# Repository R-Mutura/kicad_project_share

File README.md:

# AUTOMATION AGRIBOARD
This board features various sensors and mosules that enables easy monitoring of any environmental variable as well as control of outputs such as fans and heaters.
The board feature an ESP32 SoC that enables use of webservers and BLE configuration. This can be used to control and monitor conditions from your phone or computer.
Applications areas: Green houses and small Gardens.

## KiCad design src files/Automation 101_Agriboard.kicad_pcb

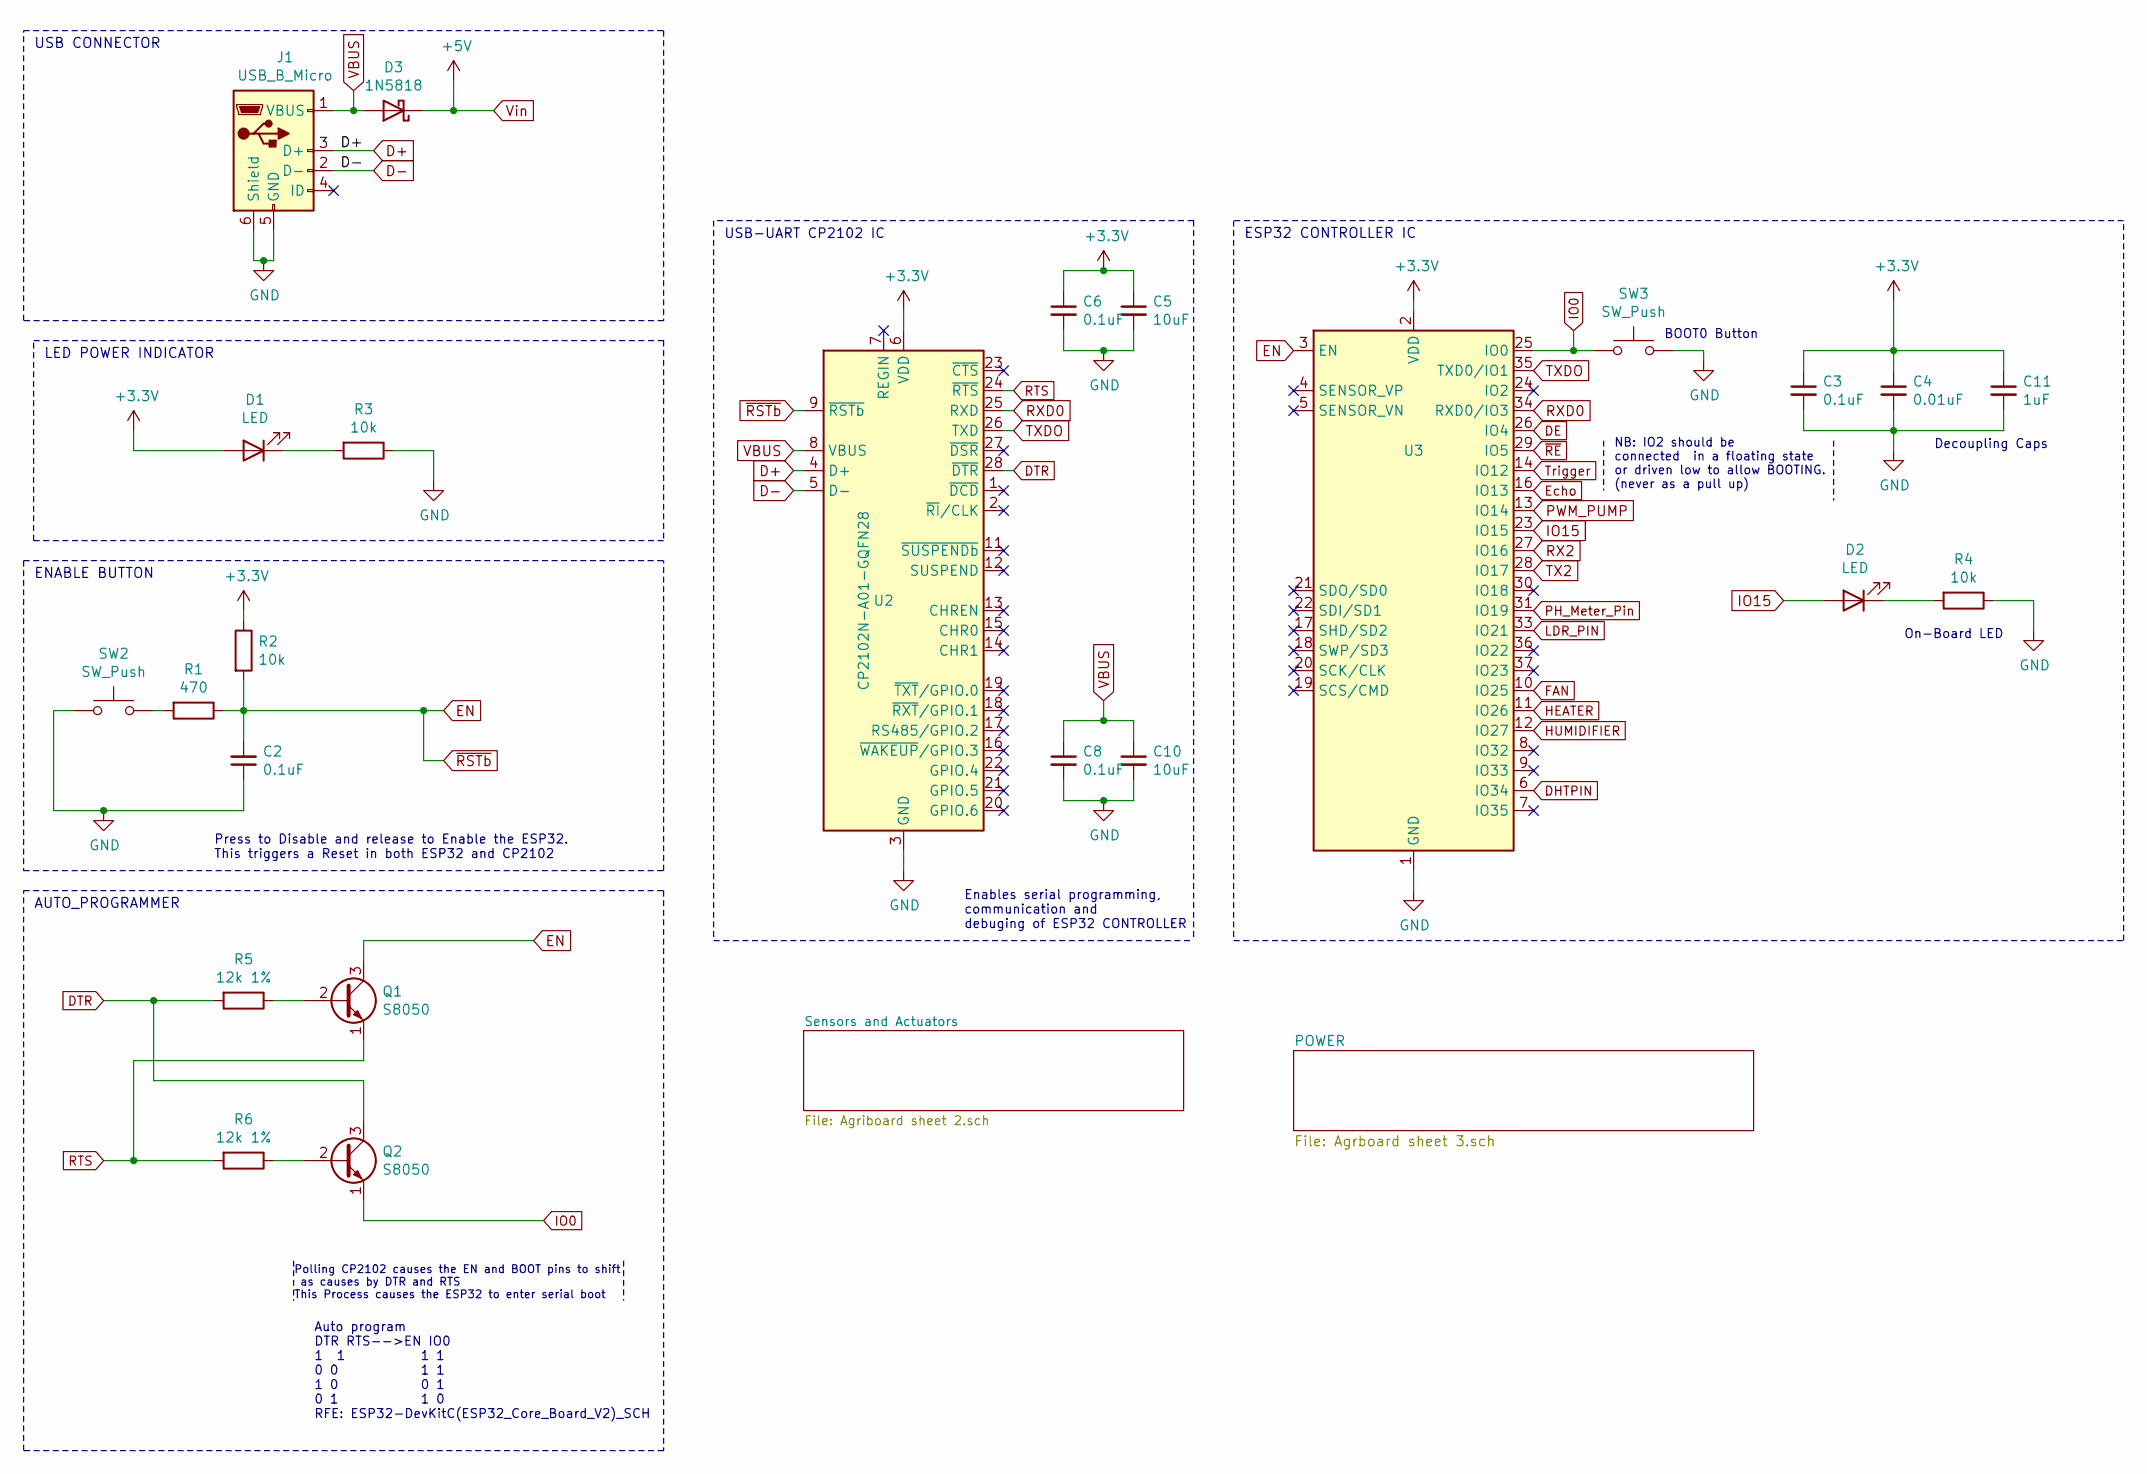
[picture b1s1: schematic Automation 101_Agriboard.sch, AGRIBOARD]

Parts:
C2, C3, C6, C8: 0.1uF; C_0402_1005Metric
C4: 0.01uF; C_0402_1005Metric
C5, C10: 10uF; C_0402_1005Metric
C11: 1uF; C_0402_1005Metric
D1, D2: LED; LED_0402_1005Metric
D3: 1N5818; D_0201_0603Metric_Pad0.64x0.40mm_HandSolder
J1: USB_B_Micro; USB_Micro-B_Molex_47346-0001
Q1, Q2: S8050; TSOT-23
R1: 470; R_0402_1005Metric_Pad0.72x0.64mm_HandSolder
R2, R3, R4: 10k; R_0402_1005Metric
R5, R6: 12k 1%; R_0402_1005Metric_Pad0.72x0.64mm_HandSolder
SW2, SW3: SW_Push; SW_SPST_B3U-1000P-B
U2: CP2102N-A01-GQFN28; QFN-28-1EP_5x5mm_P0.5mm_EP3.35x3.35mm
U3: ESP32-WROOM-32

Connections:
+3V3: C3.1, C4.1, C5.1, C6.1, C11.1, D1.2 (A), R2.1, U2.6 (VDD), U3.2 (VDD); also elsewhere on the board
D+: J1.3 (D+), U2.4 (D+)
D-: J1.2 (D-), U2.5 (D-)
DE: U3.26 (IO4); also elsewhere on the board
DHTPIN: U3.6 (IO34); also elsewhere on the board
DTR: Q2.3 (C), R5.2, U2.28 (~DTR)
EN: C2.2, Q1.3 (C), R1.1, R2.2, U2.9 (~RSTb), U3.3 (EN)
Echo: U3.16 (IO13); also elsewhere on the board
FAN: U3.10 (IO25); also elsewhere on the board
GND: C2.1, C3.2, C4.2, C5.2, C6.2, C8.2, C10.2, C11.2, J1.5 (GND), J1.6 (Shield), R3.1, R4.1, SW2.1, SW3.2, U2.3 (GND), U2.29 (GND), U3.1 (GND), U3.15 (GND), U3.38 (GND), U3.39 (GND); also elsewhere on the board
HEATER: U3.11 (IO26); also elsewhere on the board
HUMIDIFIER: U3.12 (IO27); also elsewhere on the board
IO0: Q2.1 (E), SW3.1, U3.25 (IO0)
IO15: D2.2 (A), U3.23 (IO15)
LDR_PIN: U3.33 (IO21); also elsewhere on the board
unnamed: D1.1 (K), R3.2
unnamed: D2.1 (K), R4.2
unnamed: Q1.2 (B), R5.1
unnamed: Q2.2 (B), R6.1
unnamed: R1.2, SW2.2
PH_Meter_Pin: U3.31 (IO19); also elsewhere on the board
PWM_PUMP: U3.13 (IO14); also elsewhere on the board
RTS: Q1.1 (E), R6.2, U2.24 (~RTS)
RX2: U3.27 (IO16); also elsewhere on the board
RXD0: U2.25 (RXD), U3.34 (RXD0/IO3)
TX2: U3.28 (IO17); also elsewhere on the board
TXDO: U2.26 (TXD), U3.35 (TXD0/IO1)
Trigger: U3.14 (IO12); also elsewhere on the board
VBUS: C8.1, C10.1, D3.2 (A), J1.1 (VBUS), U2.8 (VBUS)
Vin: D3.1 (K); also elsewhere on the board
~RE: U3.29 (IO5); also elsewhere on the board

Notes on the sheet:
USB CONNECTOR
LED POWER INDICATOR
ENABLE BUTTON
Press to Disable and release to Enable the ESP32. This triggers a Reset in both ESP32 and CP2102
USB-UART CP2102 IC
ESP32 CONTROLLER IC
On-Board LED
Decoupling Caps
BOOT0 Button
Auto program DTR RTS-->EN IO0 1 1 1 1 0 0 1 1 1 0 0 1 0 1 1 0 RFE: ESP32-DevKitC(ESP32_Core_Board_V2)_SCH
Enables serial programming, communication and debuging of ESP32 CONTROLLER
AUTO_PROGRAMMER
Polling CP2102 causes the EN and BOOT pins to shift as causes by DTR and RTS This Process causes the ESP32 to enter serial boot
NB: IO2 should be connected in a floating state or driven low to allow BOOTING. (never as a pull up)

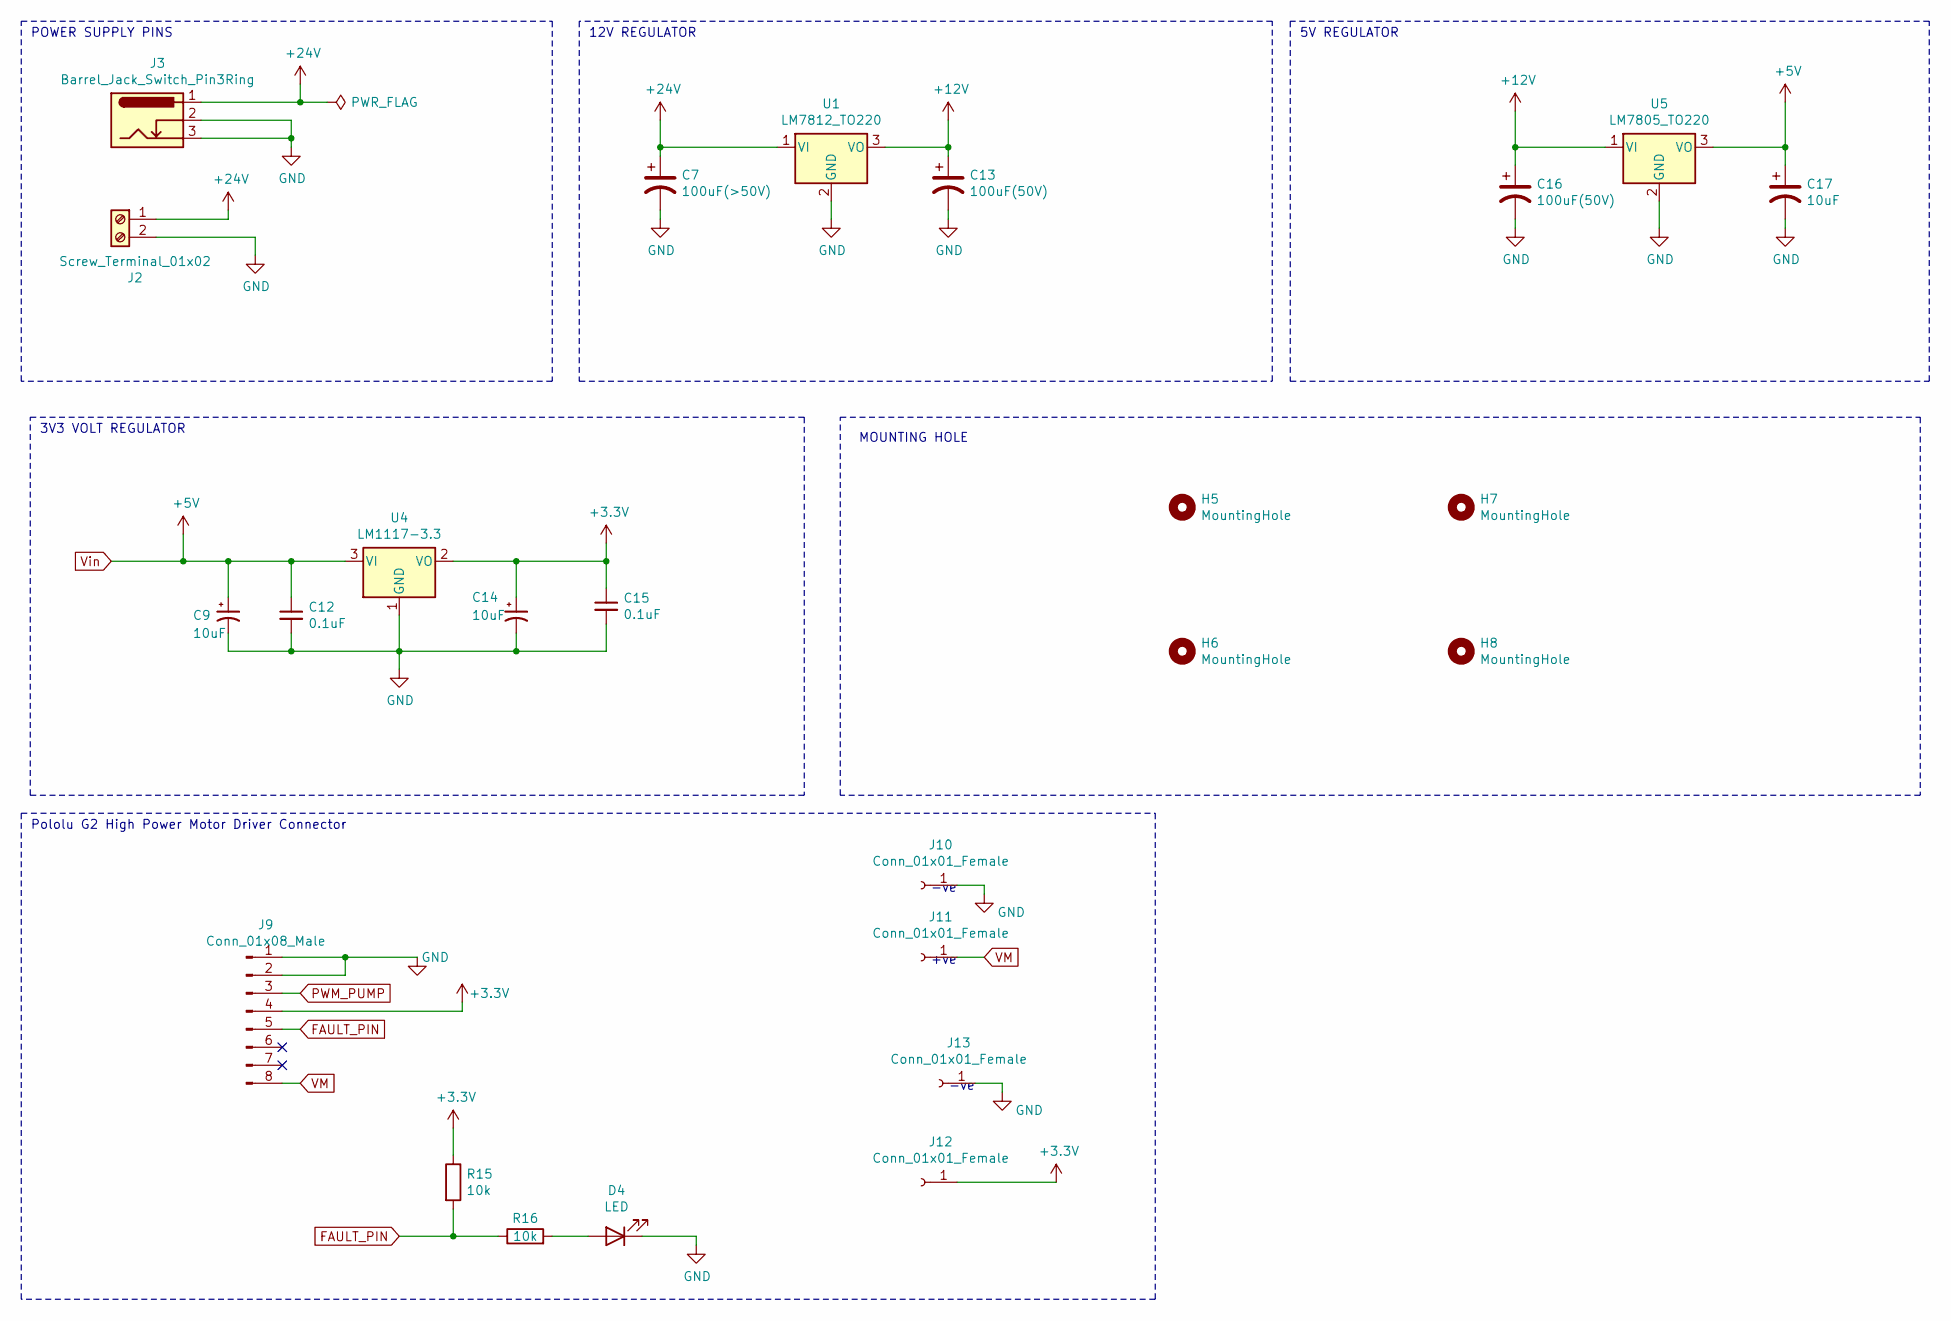
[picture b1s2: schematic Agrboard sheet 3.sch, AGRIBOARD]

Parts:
C7: 100uF(>50V); CP_Radial_D5.0mm_P2.50mm
C9, C14: 10uF; CP_EIA-1608-08_AVX-J_Pad1.25x1.05mm_HandSolder
C12, C15: 0.1uF; C_0402_1005Metric
C13, C16: 100uF(50V); CP_Radial_D5.0mm_P2.50mm
C17: 10uF; CP_Radial_D5.0mm_P2.50mm
D4: LED; LED_0805_2012Metric_Pad1.15x1.40mm_HandSolder
H5, H6, H7, H8: MountingHole; MountingHole_2.5mm
J2: Screw_Terminal_01x02; TerminalBlock_RND_205-00012_1x02_P5.00mm_Horizontal
J3: Barrel_Jack_Switch_Pin3Ring; BarrelJack_Horizontal
J9: Conn_01x08_Male; PinHeader_1x08_P2.54mm_Vertical
J10, J11, J12, J13: Conn_01x01_Female; PinHeader_1x01_P2.54mm_Vertical
R15, R16: 10k; R_0805_2012Metric_Pad1.20x1.40mm_HandSolder
U1: LM7812_TO220; TO-220-3_Vertical
U4: LM1117-3.3; SOT-223-3_TabPin2
U5: LM7805_TO220; TO-220-3_Vertical

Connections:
+3V3: C14.1, C15.1, J9.4, J12.1, R15.1, U4.2 (VO); also elsewhere on the board
+12V: C13.1, C16.1, U1.3 (VO), U5.1 (VI); also elsewhere on the board
+24V: C7.1, J2.1, J3.1, U1.1 (VI)
FAULT_PIN: J9.5, R15.2, R16.1
GND: C7.2, C9.2, C12.2, C13.2, C14.2, C15.2, C16.2, C17.2, D4.1 (K), J2.2, J3.2, J3.3, J9.1, J9.2, J10.1, J13.1, U1.2 (GND), U4.1 (GND), U5.2 (GND); also elsewhere on the board
unnamed: D4.2 (A), R16.2
PWM_PUMP: J9.3; also elsewhere on the board
VM: J9.8, J11.1
Vin: C9.1, C12.1, C17.1, U4.3 (VI), U5.3 (VO); also elsewhere on the board

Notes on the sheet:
3V3 VOLT REGULATOR
POWER SUPPLY PINS
12V REGULATOR
5V REGULATOR
-ve
+ve
Pololu G2 High Power Motor Driver Connector
MOUNTING HOLE

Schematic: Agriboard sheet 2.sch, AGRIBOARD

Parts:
C18: 0.1uF; C_0805_2012Metric_Pad1.18x1.45mm_HandSolder
H1, H2: MountingHole; MountingHole_2.5mm
J4, J6: Conn_01x04_Male; PinHeader_1x04_P2.54mm_Vertical
J5: NPK_SIGNAL_CONNECTOR; TerminalBlock_RND_205-00012_1x02_P5.00mm_Horizontal
J7: Conn_01x03_Female; PinSocket_1x03_P2.54mm_Horizontal
J8: RELAY CONN; PinSocket_1x06_P2.54mm_Vertical
J14: NPK_POWER_CONNECTOR; TerminalBlock_RND_205-00012_1x02_P5.00mm_Horizontal
Q3, Q4, Q5: 2N2222; TO-18-3
R7, R8, R9, R10, R11, R14: 10k; R_0402_1005Metric
R12: R; R_0805_2012Metric_Pad1.20x1.40mm_HandSolder
R13: R_PHOTO; R_LDR_11x9.4mm_P8.2mm_Vertical
U6: MAX3486; SOIC-8_3.9x4.9mm_P1.27mm

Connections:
+3V3: C18.1, J4.1, J6.1, J7.2, J8.6, R12.1, U6.8 (VCC); also elsewhere on the board
+12V: J14.1; also elsewhere on the board
DE: U6.3 (DE); also elsewhere on the board
DHTPIN: J6.2; also elsewhere on the board
Echo: J4.3; also elsewhere on the board
FAN: R9.2; also elsewhere on the board
FAN_RELAY: J8.3, Q4.1
GND: C18.2, J4.4, J6.4, J7.1, J8.1, J14.2, R13.2, U6.5 (GND); also elsewhere on the board
HEATER: R11.2; also elsewhere on the board
HEATER_RELAY: J8.2, Q5.1
HUMIDIFIER: R7.2; also elsewhere on the board
HUMIDIFIER_RELAY: J8.4, Q3.1
LDR_PIN: R12.2, R13.1; also elsewhere on the board
unnamed: J5.1, U6.7 (B)
unnamed: J5.2, U6.6 (A)
unnamed: Q3.2, R7.1
unnamed: Q3.3, R8.2
unnamed: Q4.2, R9.1
unnamed: Q4.3, R10.2
unnamed: Q5.2, R11.1
unnamed: Q5.3, R14.2
PH_Meter_Pin: J7.3; also elsewhere on the board
RX2: U6.1 (RO); also elsewhere on the board
TX2: U6.4 (DI); also elsewhere on the board
Trigger: J4.2; also elsewhere on the board
Vin: R8.1, R10.1, R14.1; also elsewhere on the board
~RE: U6.2 (~RE); also elsewhere on the board

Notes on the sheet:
RS485 TTL CONVERTER
PH SENSOR MODULE
this module features tremperature compensation, and analog signal procesing
TEMPERATURE/HUMIDITY SENSOR
DHT22 SENSOR
LIGHT DETECTOR
LDR SENSOR
NPK sensor connectors
WATER LVEL SENSOR(Ultra_Sonic)
On-Board LED
HEATER ACTUATOR
HUMIDIFIER ACTUATOR
FAN ACTUATOR
RELAY CONNECTOR

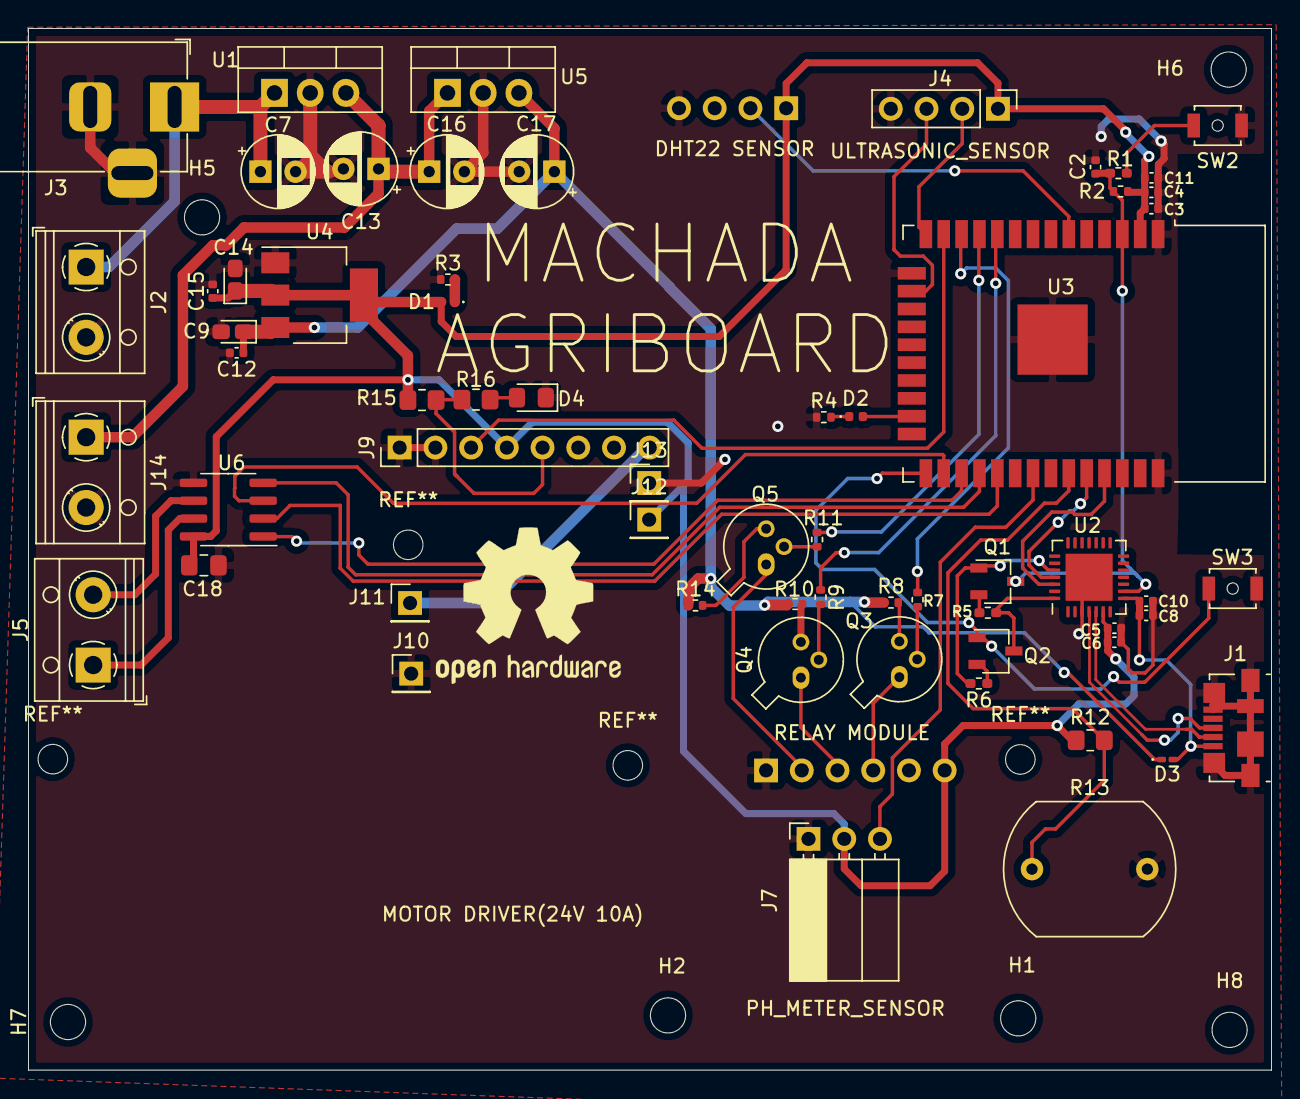
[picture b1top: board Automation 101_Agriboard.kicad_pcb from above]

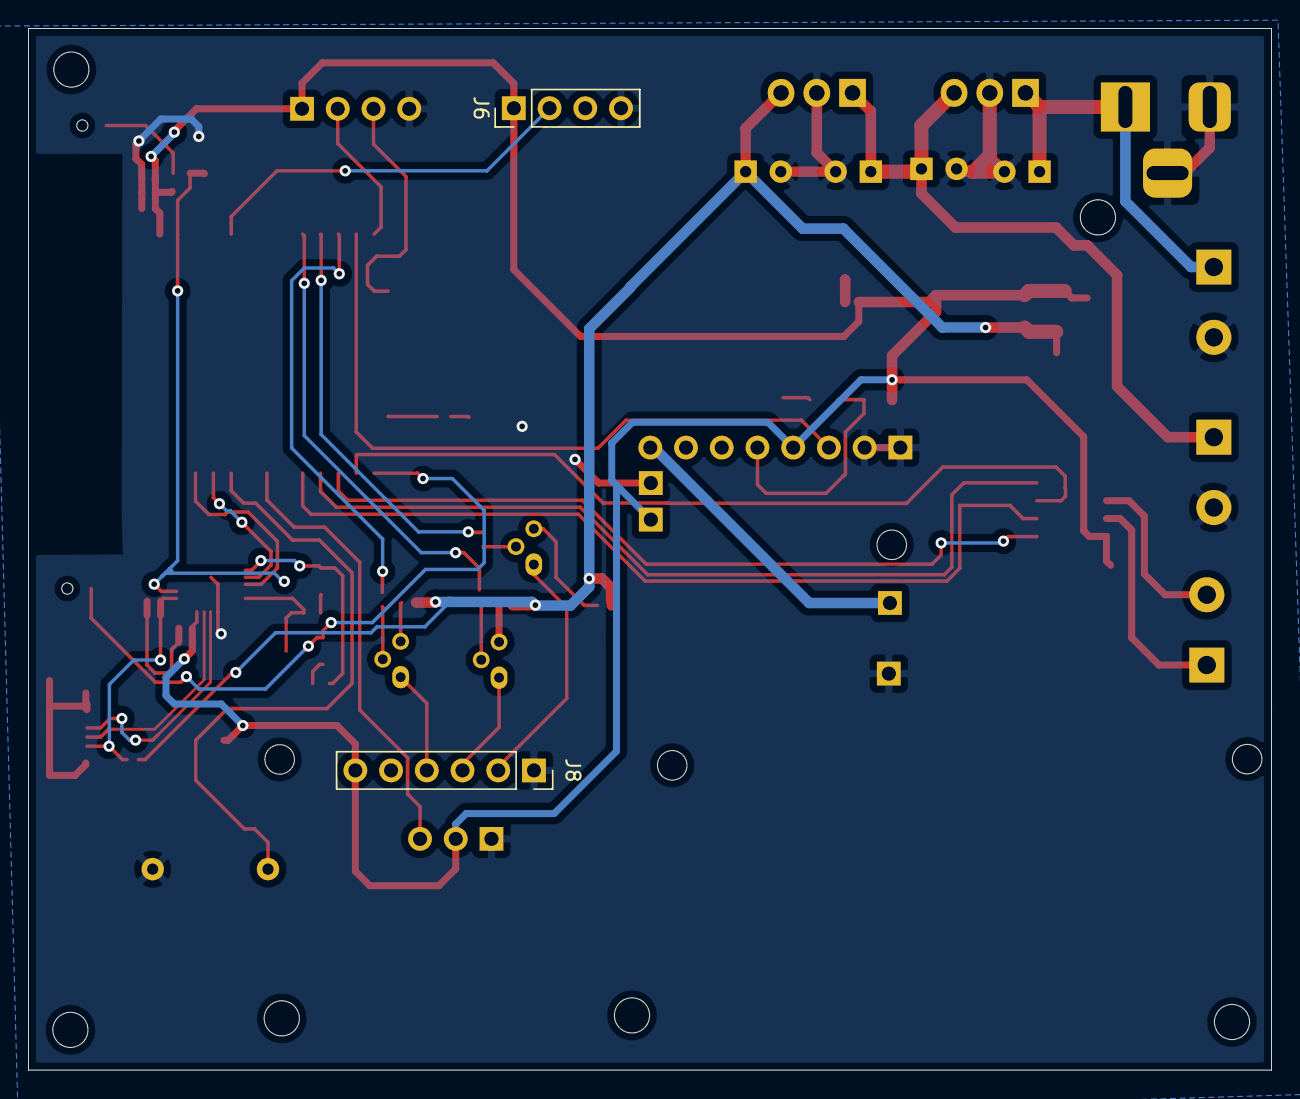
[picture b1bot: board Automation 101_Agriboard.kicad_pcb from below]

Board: 2 copper layers, 88.4 x 74.1 mm, 70 parts (2 on the bottom side), 47 nets.

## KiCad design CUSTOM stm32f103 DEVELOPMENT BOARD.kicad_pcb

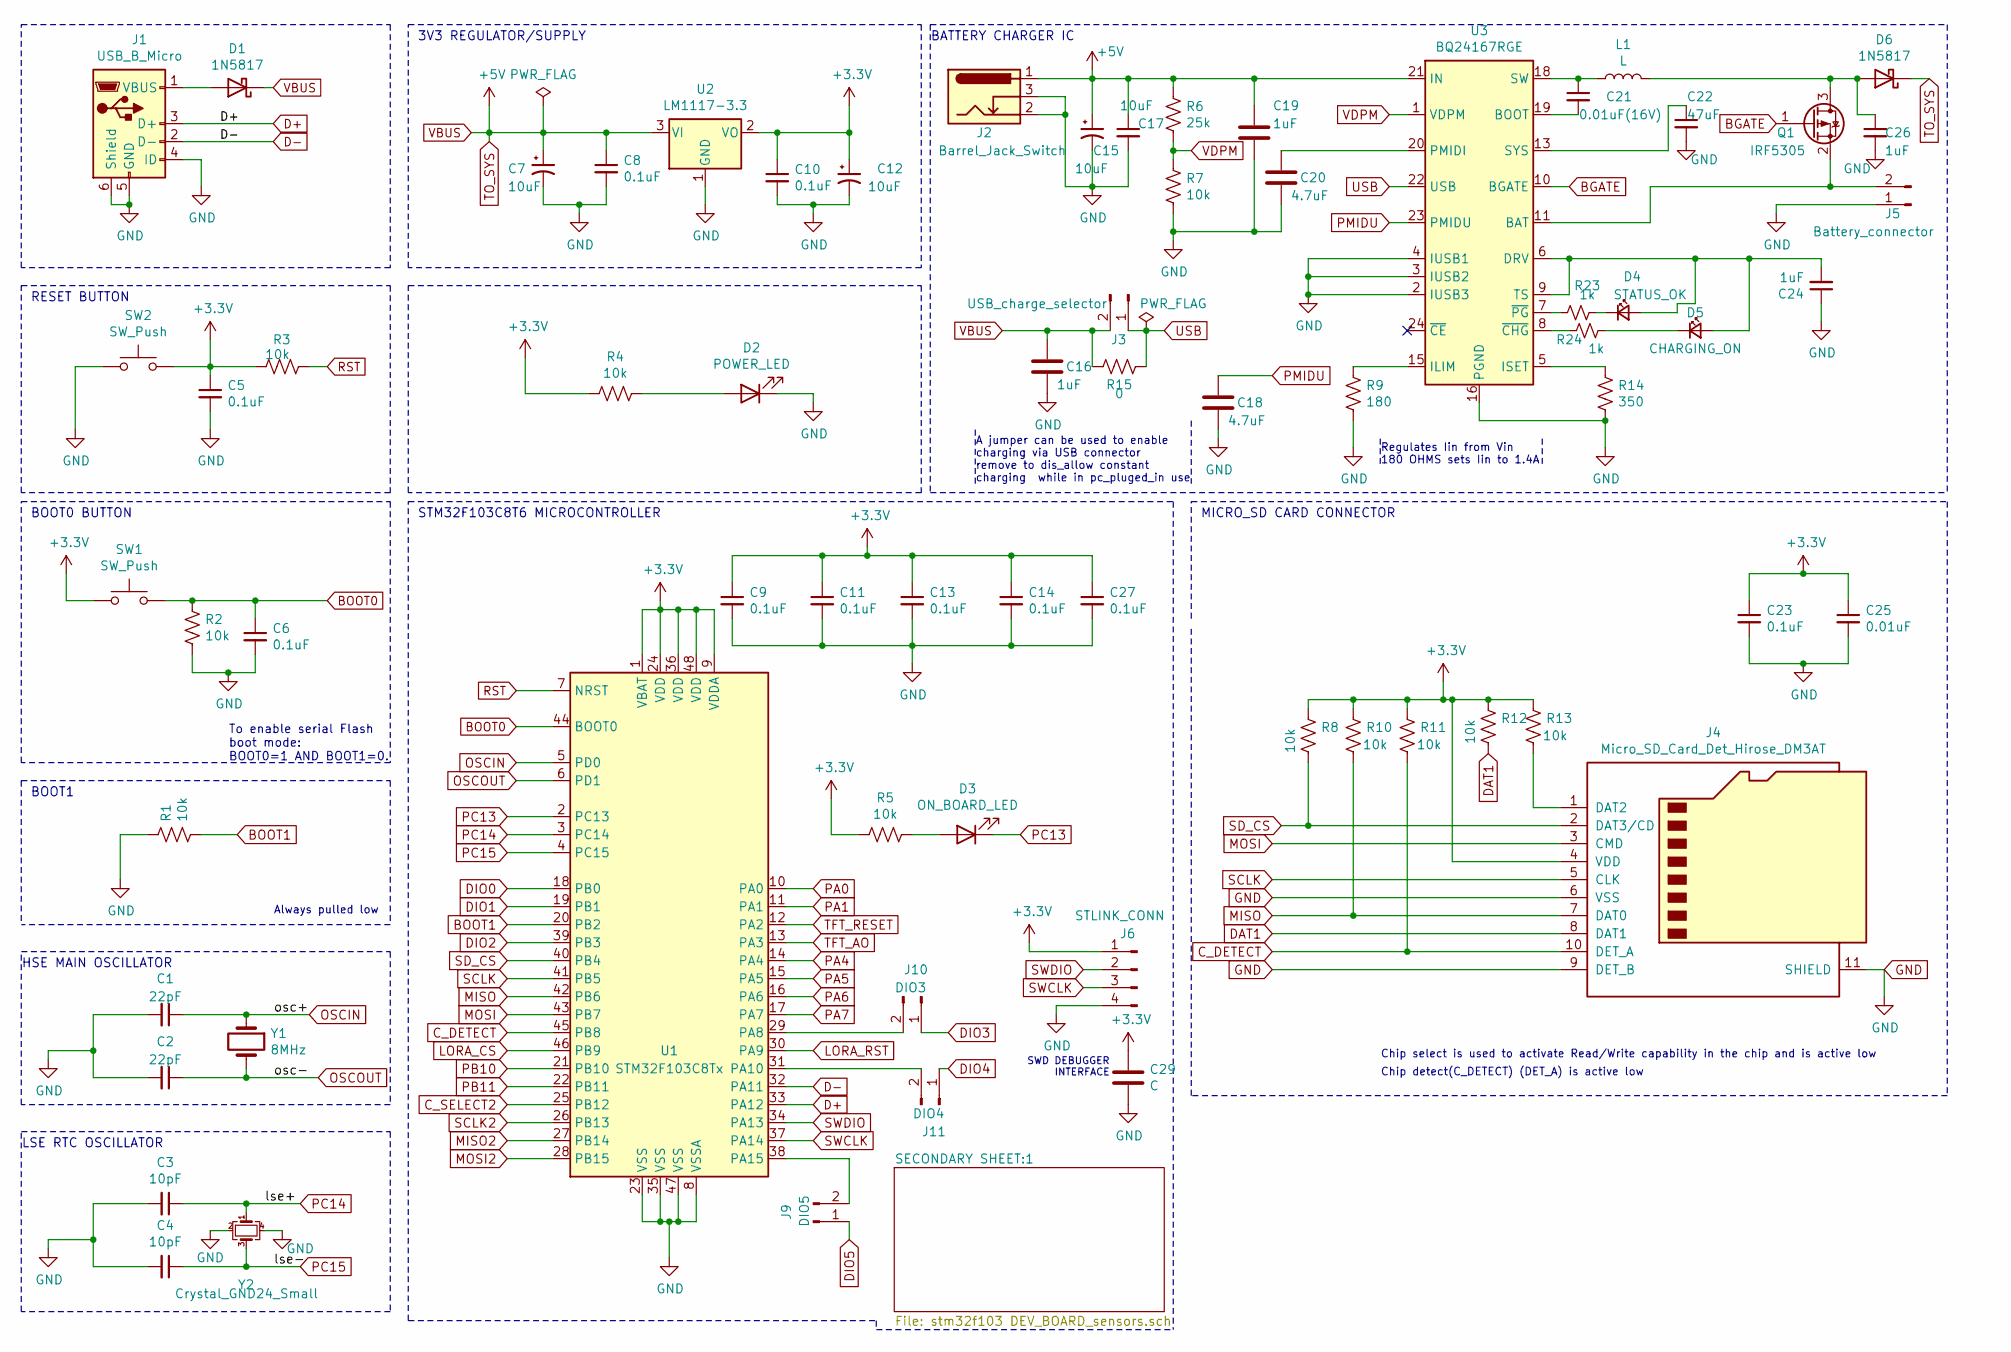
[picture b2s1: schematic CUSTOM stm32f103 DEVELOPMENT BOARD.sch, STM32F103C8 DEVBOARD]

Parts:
C1, C2: 22pF; C_0603_1608Metric
C3, C4: 10pF; C_0603_1608Metric
C5, C9, C13, C14, C27: 0.1uF; C_0402_1005Metric_Pad0.74x0.62mm_HandSolder
C6, C8: 0.1uF; C_0603_1608Metric
C7, C15: 10uF; C_0805_2012Metric; Part No. TACL106K010XTA
C10, C23: 0.1uF; C_0603_1608Metric_Pad1.08x0.95mm_HandSolder
C11: 0.1uF; C_0402_1005Metric
C12: 10uF; C_0805_2012Metric
C16, C19, C24, C26: 1uF; C_0603_1608Metric_Pad1.08x0.95mm_HandSolder
C17: 10uF; C_0603_1608Metric_Pad1.08x0.95mm_HandSolder
C18, C20: 4.7uF; C_0603_1608Metric_Pad1.08x0.95mm_HandSolder
C21: 0.01uF(16V); C_0603_1608Metric_Pad1.08x0.95mm_HandSolder
C22: 47uF; C_0603_1608Metric_Pad1.08x0.95mm_HandSolder
C25: 0.01uF; C_0603_1608Metric_Pad1.08x0.95mm_HandSolder
C29: C; C_0603_1608Metric_Pad1.08x0.95mm_HandSolder
D1: 1N5817; D_0603_1608Metric_Pad1.05x0.95mm_HandSolder
D2: POWER_LED; D_0603_1608Metric_Pad1.05x0.95mm_HandSolder
D3: ON_BOARD_LED; D_0603_1608Metric_Pad1.05x0.95mm_HandSolder
D4: STATUS_OK; D_0603_1608Metric_Pad1.05x0.95mm_HandSolder
D5: CHARGING_ON; D_0603_1608Metric_Pad1.05x0.95mm_HandSolder
D6: 1N5817; D_0603_1608Metric
J1: USB_B_Micro; USB_Micro-B_Molex_47346-0001
J2: Barrel_Jack_Switch; BarrelJack_Horizontal
J3: USB_charge_selector; PinHeader_1x02_P2.54mm_Vertical_SMD_Pin1Left
J4: Micro_SD_Card_Det_Hirose_DM3AT; microSD_HC_Hirose_DM3D-SF
J5: Battery_connector; JST_EH_B2B-EH-A_1x02_P2.50mm_Vertical
J6: STLINK_CONN; PinHeader_1x04_P2.54mm_Vertical
J9: DIO5; PinHeader_1x02_P2.54mm_Vertical_SMD_Pin1Left
J10: DIO3; PinHeader_1x02_P2.54mm_Vertical_SMD_Pin1Left
J11: DIO4; PinHeader_1x02_P2.54mm_Vertical_SMD_Pin1Left
L1: L; L_0603_1608Metric_Pad1.05x0.95mm_HandSolder
Q1: IRF5305; TO-263-2; part No. 942-IRF5305STRLPBF
R1, R2, R3, R4, R5, R7, R8, R10, R11, R12, R13: 10k; R_0603_1608Metric_Pad0.98x0.95mm_HandSolder
R6: 25k; R_0603_1608Metric_Pad0.98x0.95mm_HandSolder
R9: 180; R_0603_1608Metric_Pad0.98x0.95mm_HandSolder
R14: 350; R_0603_1608Metric_Pad0.98x0.95mm_HandSolder
R15: 0; R_0603_1608Metric_Pad0.98x0.95mm_HandSolder
R23, R24: 1k; R_0402_1005Metric_Pad0.72x0.64mm_HandSolder
SW1: SW_Push; SW_SPST_B3U-1000P-B
SW2: SW_Push; SW_SPST_B3U-1000P
U1: STM32F103C8Tx; LQFP-48_7x7mm_P0.5mm
U2: LM1117-3.3; SOT-223-3_TabPin2
U3: BQ24167RGE; Texas_RGE0024H_EP2.7x2.7mm_ThermalVias
Y1: 8MHz; Crystal_SMD_HC49-SD; Part No. 9C-8.000MAAE-T
Y2: Crystal_GND24_Small; Crystal_SMD_SeikoEpson_MA406-4Pin_11.7x4.0mm

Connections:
A0: U1.13 (PA3); also elsewhere on the board
BGATE: Q1.1 (G), U3.10 (BGATE)
BOOT0: C6.1, R2.1, SW1.2, U1.44 (BOOT0)
BOOT1: R1.2, U1.20 (PB2)
CS: U1.25 (PB12); also elsewhere on the board
C_DETECT: J4.10 (DET_A), R11.2, U1.45 (PB8)
D+: J1.3 (D+), U1.33 (PA12)
D-: J1.2 (D-), U1.32 (PA11)
DAT1: J4.8 (DAT1), R12.2
DIO0: U1.18 (PB0); also elsewhere on the board
DIO1: U1.19 (PB1); also elsewhere on the board
DIO2: U1.39 (PB3); also elsewhere on the board
DIO3: J10.1; also elsewhere on the board
DIO4: J11.1; also elsewhere on the board
DIO5: J9.1; also elsewhere on the board
GND: C1.2, C2.2, C3.2, C4.2, C5.2, C6.2, C7.2, C8.2, C9.2, C10.2, C11.2, C12.2, C13.2, C14.2, C15.2, C16.2, C17.2, C18.2, C19.2, C20.2, C22.2, C23.2, C24.1, C25.2, C26.2, C27.2, C29.2, D2.1 (K), J1.4 (ID), J1.5 (GND), J1.6 (Shield), J2.2, J2.3, J4.6 (VSS), J4.9 (DET_B), J4.11 (SHIELD), J5.1, J6.4, R1.1, R2.2, R7.2, R9.2, R14.2, SW2.1, U1.8 (VSSA), U1.23 (VSS), U1.35 (VSS), U1.47 (VSS), U2.1 (GND), U3.2 (IUSB3), U3.3 (IUSB2), U3.4 (IUSB1), U3.16 (PGND), U3.17 (PGND), U3.25 (PGND), Y2.2, Y2.4; also elsewhere on the board
LORA_CS: U1.46 (PB9); also elsewhere on the board
LORA_RST: U1.30 (PA9); also elsewhere on the board
MISO: J4.7 (DAT0), R10.2, U1.42 (PB6); also elsewhere on the board
MOSI: J4.3 (CMD), U1.43 (PB7); also elsewhere on the board
MOSI2: U1.28 (PB15); also elsewhere on the board
unnamed: C20.1, U3.20 (PMIDI)
unnamed: C21.1, L1.1, U3.18 (SW)
unnamed: C21.2, U3.19 (BOOT)
unnamed: C22.1, U3.13 (SYS), U3.14 (SYS)
unnamed: C24.2, D4.2 (A), D5.2 (A), U3.6 (DRV), U3.9 (TS)
unnamed: C26.1, D6.2 (A), L1.2, Q1.3 (D)
unnamed: D1.2 (A), J1.1 (VBUS)
unnamed 29: D2.2 (A), R4.1; also elsewhere on the board
unnamed 30: D3.2 (A), R5.1; also elsewhere on the board
unnamed: D4.1 (K), R23.1
unnamed: D5.1 (K), R24.1
unnamed: J4.1 (DAT2), R13.2
unnamed: J5.2, Q1.2 (S), U3.11 (BAT), U3.12 (BAT)
unnamed: J9.2, U1.38 (PA15)
unnamed: J10.2, U1.29 (PA8)
unnamed: J11.2, U1.31 (PA10)
unnamed: R9.1, U3.15 (ILIM)
unnamed: R14.1, U3.5 (ISET)
unnamed: R23.2, U3.7 (~PG)
unnamed: R24.2, U3.8 (~CHG)
OSCIN: C1.1, U1.5 (PD0), Y1.1
OSCOUT: C2.1, U1.6 (PD1), Y1.2
PA0: U1.10 (PA0); also elsewhere on the board
PA1: U1.11 (PA1); also elsewhere on the board
PA4: U1.14 (PA4); also elsewhere on the board
PA5: U1.15 (PA5); also elsewhere on the board
PA6: U1.16 (PA6); also elsewhere on the board
PA7: U1.17 (PA7); also elsewhere on the board
PB10: U1.21 (PB10); also elsewhere on the board
PB11: U1.22 (PB11); also elsewhere on the board
PC13: D3.1 (K), U1.2 (PC13); also elsewhere on the board
PC14: C3.1, U1.3 (PC14), Y2.1
PC15: C4.1, U1.4 (PC15), Y2.3
PMIDU: C18.1, U3.23 (PMIDU)
RST: R3.2, U1.7 (NRST)
SCK: U1.26 (PB13); also elsewhere on the board
SCLK: J4.5 (CLK), U1.41 (PB5); also elsewhere on the board
SD_CS: J4.2 (DAT3/CD), R8.2, U1.40 (PB4)
SWCLK: J6.3, U1.37 (PA14)
SWDIO: J6.2, U1.34 (PA13)
TFT_RESET: U1.12 (PA2); also elsewhere on the board
TO_SYS: C7.1, C8.1, C15.1, C16.1, C17.1, C19.1, D1.1 (K), D6.1 (K), J2.1, J3.2, R6.1, R15.1, U2.3 (VI), U3.21 (IN); also elsewhere on the board
USB: J3.1, R15.2, U3.22 (USB)
VDPM: R6.2, R7.1, U3.1 (VDPM)

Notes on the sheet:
Chip detect(C_DETECT) (DET_A) is active low
Chip select is used to activate Read/Write capability in the chip and is active low
MICRO_SD CARD CONNECTOR
To enable serial Flash boot mode: BOOT0=1 AND BOOT1=0.
Regulates Iin from Vin 180 OHMS sets Iin to 1.4A
3V3 REGULATOR/SUPPLY
RESET BUTTON
BOOT0 BUTTON
BOOT1
Always pulled low
HSE MAIN OSCILLATOR
LSE RTC OSCILLATOR
STM32F103C8T6 MICROCONTROLLER
BATTERY CHARGER IC
A jumper can be used to enable charging via USB connector remove to dis_allow constant charging while in pc_pluged_in use
SWD DEBUGGER INTERFACE

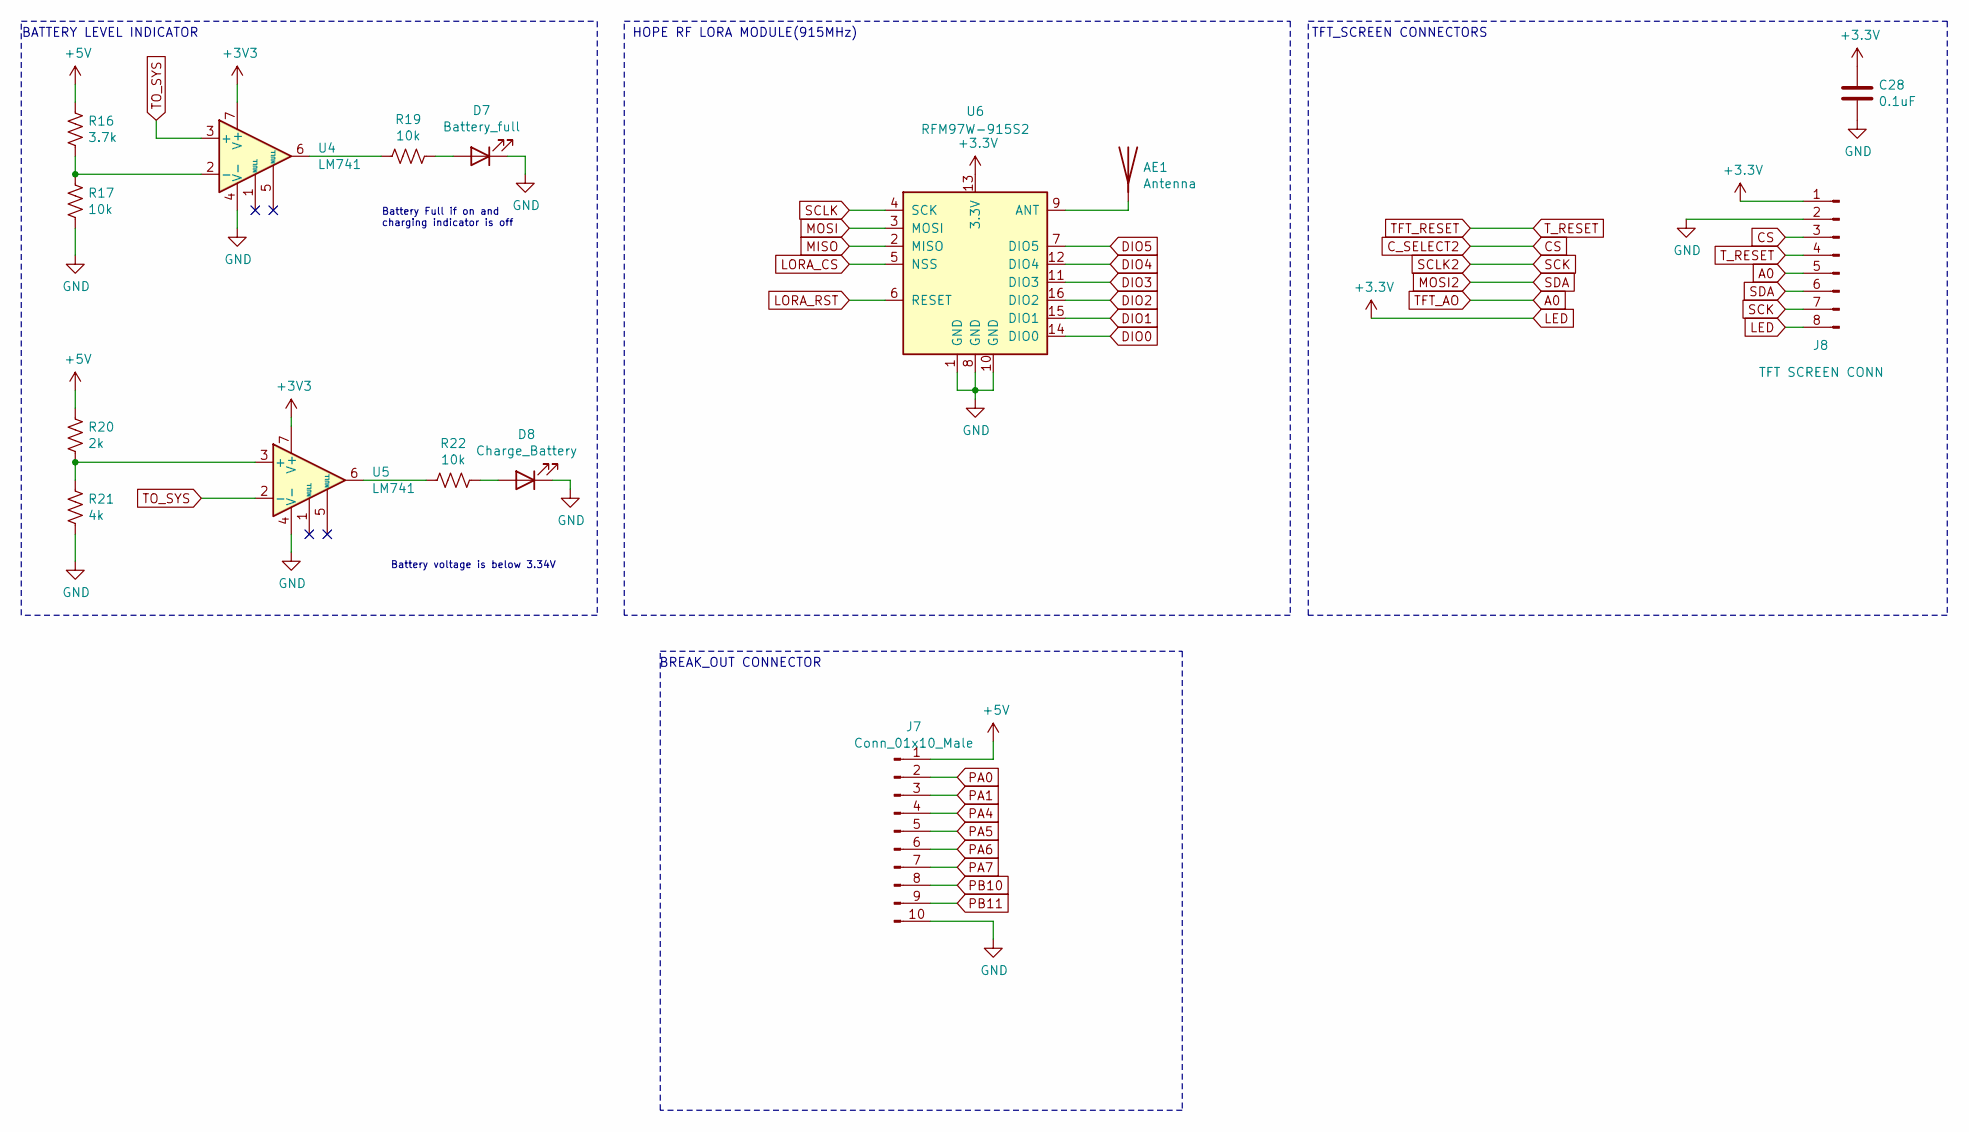
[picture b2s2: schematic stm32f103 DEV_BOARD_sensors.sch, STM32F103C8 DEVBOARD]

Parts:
AE1: Antenna; U.FL_Hirose_U.FL-R-SMT-1_Vertical
C28: 0.1uF; C_0603_1608Metric_Pad1.08x0.95mm_HandSolder
D7: Battery_full; D_0603_1608Metric_Pad1.05x0.95mm_HandSolder
D8: Charge_Battery; D_0603_1608Metric_Pad1.05x0.95mm_HandSolder
J7: Conn_01x10_Male; PinHeader_1x10_P2.54mm_Vertical
J8: TFT SCREEN CONN; Molex_KK-254_AE-6410-08A_1x08_P2.54mm_Vertical
R16: 3.7k; R_0603_1608Metric_Pad0.98x0.95mm_HandSolder
R17, R19, R22: 10k; R_0603_1608Metric_Pad0.98x0.95mm_HandSolder
R20: 2k; R_0603_1608Metric_Pad0.98x0.95mm_HandSolder
R21: 4k; R_0603_1608Metric_Pad0.98x0.95mm_HandSolder
U4, U5: LM741; SOIC-8_3.9x4.9mm_P1.27mm
U6: RFM97W-915S2; HOPERF_RFM9XW_SMD

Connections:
A0: J8.5; also elsewhere on the board
CS: J8.3; also elsewhere on the board
DIO0: U6.14 (DIO0); also elsewhere on the board
DIO1: U6.15 (DIO1); also elsewhere on the board
DIO2: U6.16 (DIO2); also elsewhere on the board
DIO3: U6.11 (DIO3); also elsewhere on the board
DIO4: U6.12 (DIO4); also elsewhere on the board
DIO5: U6.7 (DIO5); also elsewhere on the board
GND: C28.2, D7.1 (K), D8.1 (K), J7.10, J8.2, R17.2, R21.2, U4.4 (V-), U5.4 (V-), U6.1 (GND), U6.8 (GND), U6.10 (GND); also elsewhere on the board
LORA_CS: U6.5 (NSS); also elsewhere on the board
LORA_RST: U6.6 (RESET); also elsewhere on the board
MISO: U6.2 (MISO); also elsewhere on the board
MOSI: U6.3 (MOSI); also elsewhere on the board
MOSI2: J8.6; also elsewhere on the board
unnamed: AE1.1, U6.9 (ANT)
unnamed: D7.2 (A), R19.2
unnamed: D8.2 (A), R22.2
unnamed: R16.2, R17.1, U4.2 (-)
unnamed: R19.1, U4.6
unnamed: R20.2, R21.1, U5.3 (+)
unnamed: R22.1, U5.6
PA0: J7.2; also elsewhere on the board
PA1: J7.3; also elsewhere on the board
PA4: J7.4; also elsewhere on the board
PA5: J7.5; also elsewhere on the board
PA6: J7.6; also elsewhere on the board
PA7: J7.7; also elsewhere on the board
PB10: J7.8; also elsewhere on the board
PB11: J7.9; also elsewhere on the board
SCK: J8.7; also elsewhere on the board
SCLK: U6.4 (SCK); also elsewhere on the board
TFT_RESET: J8.4; also elsewhere on the board
TO_SYS: J7.1, R16.1, R20.1, U4.3 (+), U5.2 (-); also elsewhere on the board

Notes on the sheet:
BATTERY LEVEL INDICATOR
Battery Full if on and charging indicator is off
Battery voltage is below 3.34V
HOPE RF LORA MODULE(915MHz)
TFT_SCREEN CONNECTORS
BREAK_OUT CONNECTOR

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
